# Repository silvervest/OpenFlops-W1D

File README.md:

# OpenFlops W1D
OpenFlops is an Open Hardware Floppy Disk Drive emulator/simulator.

OpenFlops W1D is a complete modification for the original OpenFlops specifically configured for use replacing the flaky Citizen W1D floppy drives, popularly used in Compaq LTE Elite laptops.

For a lot more detail, installation and usage guides, visit https://silvestron.com/openflops-w1d/

## Specifics to W1D

While this design is specifically made for the W1D when used in an LTE Elite laptop, it definitely can be used with any other floppy drive that uses the 26-pin FPC connector, it just may not fit in the same space. Heed caution.

Additionally, I made this with a few specific parts in mind - they are as follows:

* J1 - 26-pin FPC connector, part no. PCB-C5-26-SA-SMT
* J2 - USB-A port, part no. GCT USB1046
* J7 - microSD slot, part no. TF-114
* OLED - Any generic 128x64 0.96" OLED (WAVGAT on AliExpress)
* SPKR1 - Piezo buzzer, part no. CPT-9019S-SMT-TR
* SW3 - Slide switch, part no. MSK-12C02

## The rest of this README is from upstream OpenFlops!

See https://github.com/SukkoPera/OpenFlops/

### Summary
From [Wikipedia](https://en.wikipedia.org/wiki/Floppy_disk_hardware_emulator):
> Older models of computers, electronic keyboards and industrial automation often used floppy disk drives for data transfer. Older equipment may be difficult to replace or upgrade because of cost, requirement for continuous availability or unavailable upgrades. Proper operation may require operating system, software and data to be read and written from and to floppies, forcing users to maintain floppy drives on supporting systems.

> Floppy disks and floppy drives are gradually going out of production, and replacement of malfunctioning drives, and the systems hosting them, is becoming increasingly difficult. Floppy disks themselves are fragile, or may need to be replaced often. An alternative is to use a floppy disk hardware emulator, a device which appears to be a standard floppy drive to the old equipment by interfacing directly to the floppy disk controller, while storing data in another medium such as a USB thumb drive, Secure Digital card, or a shared drive on a computer network. Emulators can also be used as a higher-performance replacement for mechanical floppy disk drives. 

OpenFlops is an Open Hardware implementation of such an emulator, inspired from the ubiquitous Gotek hardware. It is designed to run the [FlashFloppy](https://github.com/keirf/FlashFloppy) firmware, which gives it several improvements over the original Gotek:
- Can be installed on [many different platforms](https://github.com/keirf/FlashFloppy/wiki/Host-Platforms)
- Directly supports a [wide range of image formats](https://github.com/keirf/FlashFloppy/wiki/Image-Formats)
- [Flexible track layout](https://github.com/keirf/FlashFloppy/wiki/Track-Layouts) for Raw Sector Images
- [Extremely configurable](https://github.com/keirf/FlashFloppy/wiki/FF.CFG-Configuration-File)
- Supports [AutoSwap](https://github.com/keirf/FF_AutoSwap) for games with a large number of disks
- Easily accessible pin headers for connection of a [i2c display](https://github.com/keirf/FlashFloppy/wiki/Hardware-Mods#lcd-display) (either OLED or LCD), [rotary encoder](https://github.com/keirf/FlashFloppy/wiki/Hardware-Mods#rotary-encoder) (including power)
- Built-in amplified speaker, or easily-accessible pin header for an external one
- USB connector can either be soldered on the board or connected to a pin header
- Connected Motor signal
- Emulates two drives at the same time (Not yet supported by the firmware, but [it will come](https://github.com/keirf/FlashFloppy/wiki/Donations))
- Has additional 3.3V, 5V and GND power pins
- And hey, it's Open Hardware!

All of this comes in the same form factor (and mounting holes) as the board installed in the original Gotek, hence it can be easily installed in any shell or enclosure designed for it.

### Assembly and Installation
Solder all components to the board. I suggest starting with the main microcontroller (U3), as it uses an LQFP package which is tricky to solder: the recommended technique is drag soldering, there are many videos about that on YouTube, so please look there for advice. I recommend soldering the bare minimum components needed for programming and then trying to flash it right away. This way you will be able to fix your soldering without too many components getting in the way, if needed. You will need a USB/TTL Serial converter for this: one with 3.3V I/O level is recommended, but a 5V one can be used, too (most pins on STM32 microcontrollers are 5V-tolerant, so don't worry, it's not a bad hack!). You shouldn't pay more than 1-2€ for it in any case, anyway. So, when you are ready:

- Solder U3, Y1, C3 and C5, then the programming header (the top one with power, BOOT0, TX, RX, etc.)
- Check for shorts on the 3.3V power lines, you can easily do this on the pads for C6-C10
- If your USB/Serial adapter has a 3.3V output, connect it to 3.3V on the power header, then connect ground, RX and TX
- If no 3.3V output is available, solder U4 and power the board through the 5V pin on the power header

Now you should be able to [program the STM32 microcontroller](https://github.com/keirf/FlashFloppy/wiki/Firmware-Programming). If you have difficultes you can try adding R10 (and C4) and maybe a few of C6-C10, but most likely the problem will be with the solder joints on U3, as soldering this kind of package manually is never easy, so please get a lens (or even better, a microscope) and double-check your job.

The serial adapter is only necessary for the first flashing. Subsequent updates [can be done easily via USB](https://github.com/keirf/FlashFloppy/wiki/Firmware-Update).

Note that most components are necessary, but there are a few you can skip if you are feeling lazy:
- If you are not interested in the head movement sound, you can skip the following components: SPK1, D2, R5, R6, Q7.
- If your LCD/OLED display already has pull-up resistors for the SDA/SCK lines (most do), you can skip R3 and R4.

### Configuration
Please refer to the FlashFloppy wiki for the [initial setup](https://github.com/keirf/FlashFloppy/wiki/Initial-Setup) and an overview of the [available configuration options](https://github.com/keirf/FlashFloppy/wiki/FF.CFG-Configuration-File).

Some options that you will want to override the default values of, in order to take advantage of all the features OpenFlops provides, are the following:
- `motor-delay`
- `rotary`
- `display-type`

### Releases
If you want to get this board produced, you are recommended to get [the latest release](https://github.com/SukkoPera/OpenFlops/releases) rather than the current git version, as the latter might be under development and is not guaranteed to be working.

Every release is accompanied by its Bill Of Materials (BOM) file and any relevant notes about it, which you are recommended to read carefully.

### License
The OpenFlops documentation, including the design itself, is copyright &copy; SukkoPera 2019-2020.

OpenFlops is Open Hardware licensed under the [CERN OHL v. 1.2](http://ohwr.org/cernohl).

You may redistribute and modify this documentation under the terms of the CERN OHL v.1.2. This documentation is distributed *as is* and WITHOUT ANY EXPRESS OR IMPLIED WARRANTIES whatsoever with respect to its functionality, operability or use, including, without limitation, any implied warranties OF MERCHANTABILITY, SATISFACTORY QUALITY, FITNESS FOR A PARTICULAR PURPOSE or infringement. We expressly disclaim any liability whatsoever for any direct, indirect, consequential, incidental or special damages, including, without limitation, lost revenues, lost profits, losses resulting from business interruption or loss of data, regardless of the form of action or legal theory under which the liability may be asserted, even if advised of the possibility or likelihood of such damages.

A copy of the full license is included in file [LICENSE.pdf](LICENSE.pdf), please refer to it for applicable conditions. In order to properly deal with its terms, please see file [LICENSE_HOWTO.pdf](LICENSE_HOWTO.pdf).

The contact points for information about manufactured Products (see section 4.2) are listed in file [PRODUCT.md](PRODUCT.md).

Any modifications made by Licensees (see section 3.4.b) shall be recorded in file [CHANGES.md](CHANGES.md).

The Documentation Location of the original project is https://github.com/SukkoPera/OpenFlops/.

### Support the Project
Since the project is open you are free to get the PCBs made by your preferred manufacturer, however in case you want to support the development, you can order them from PCBWay through this link:

You get my gratitude and cheap, professionally-made and good quality PCBs, I get some credit that will help with this and [other projects](https://www.pcbway.com/project/member/shareproject/?bmbid=41100). You won't even have to worry about the various PCB options, it's all pre-configured for you!

Also, if you still have to register to that site, [you can use this link](https://www.pcbway.com/setinvite.aspx?inviteid=41100) to get some bonus initial credit (and yield me some more).

Again, if you want to use another manufacturer, feel free to, don't feel obligated :). But then you can buy me a coffee if you want:

### Get Help
If you need help or have questions, you can join [the official Telegram group](https://t.me/joinchat/HUHdWBC9J9JnYIrvTYfZmg).

### Thanks
- H.M for publishing the [original Gotek schematics](doc/gotek_usb-fde_block-diagram.jpg)
- [keirf](https://github.com/keirf) for FlashFloppy
- Brian Allan for suggesting some improvements for the Speaker circuit
- Ray Bellis for suggesting adding pin headers for the USB port and speaker
- Mario Babeu for suggesting to line up the orientation of LD1 and LD2
- Patrick Kerkhof for sending me a lot of original Gotek housing for dimensional testing

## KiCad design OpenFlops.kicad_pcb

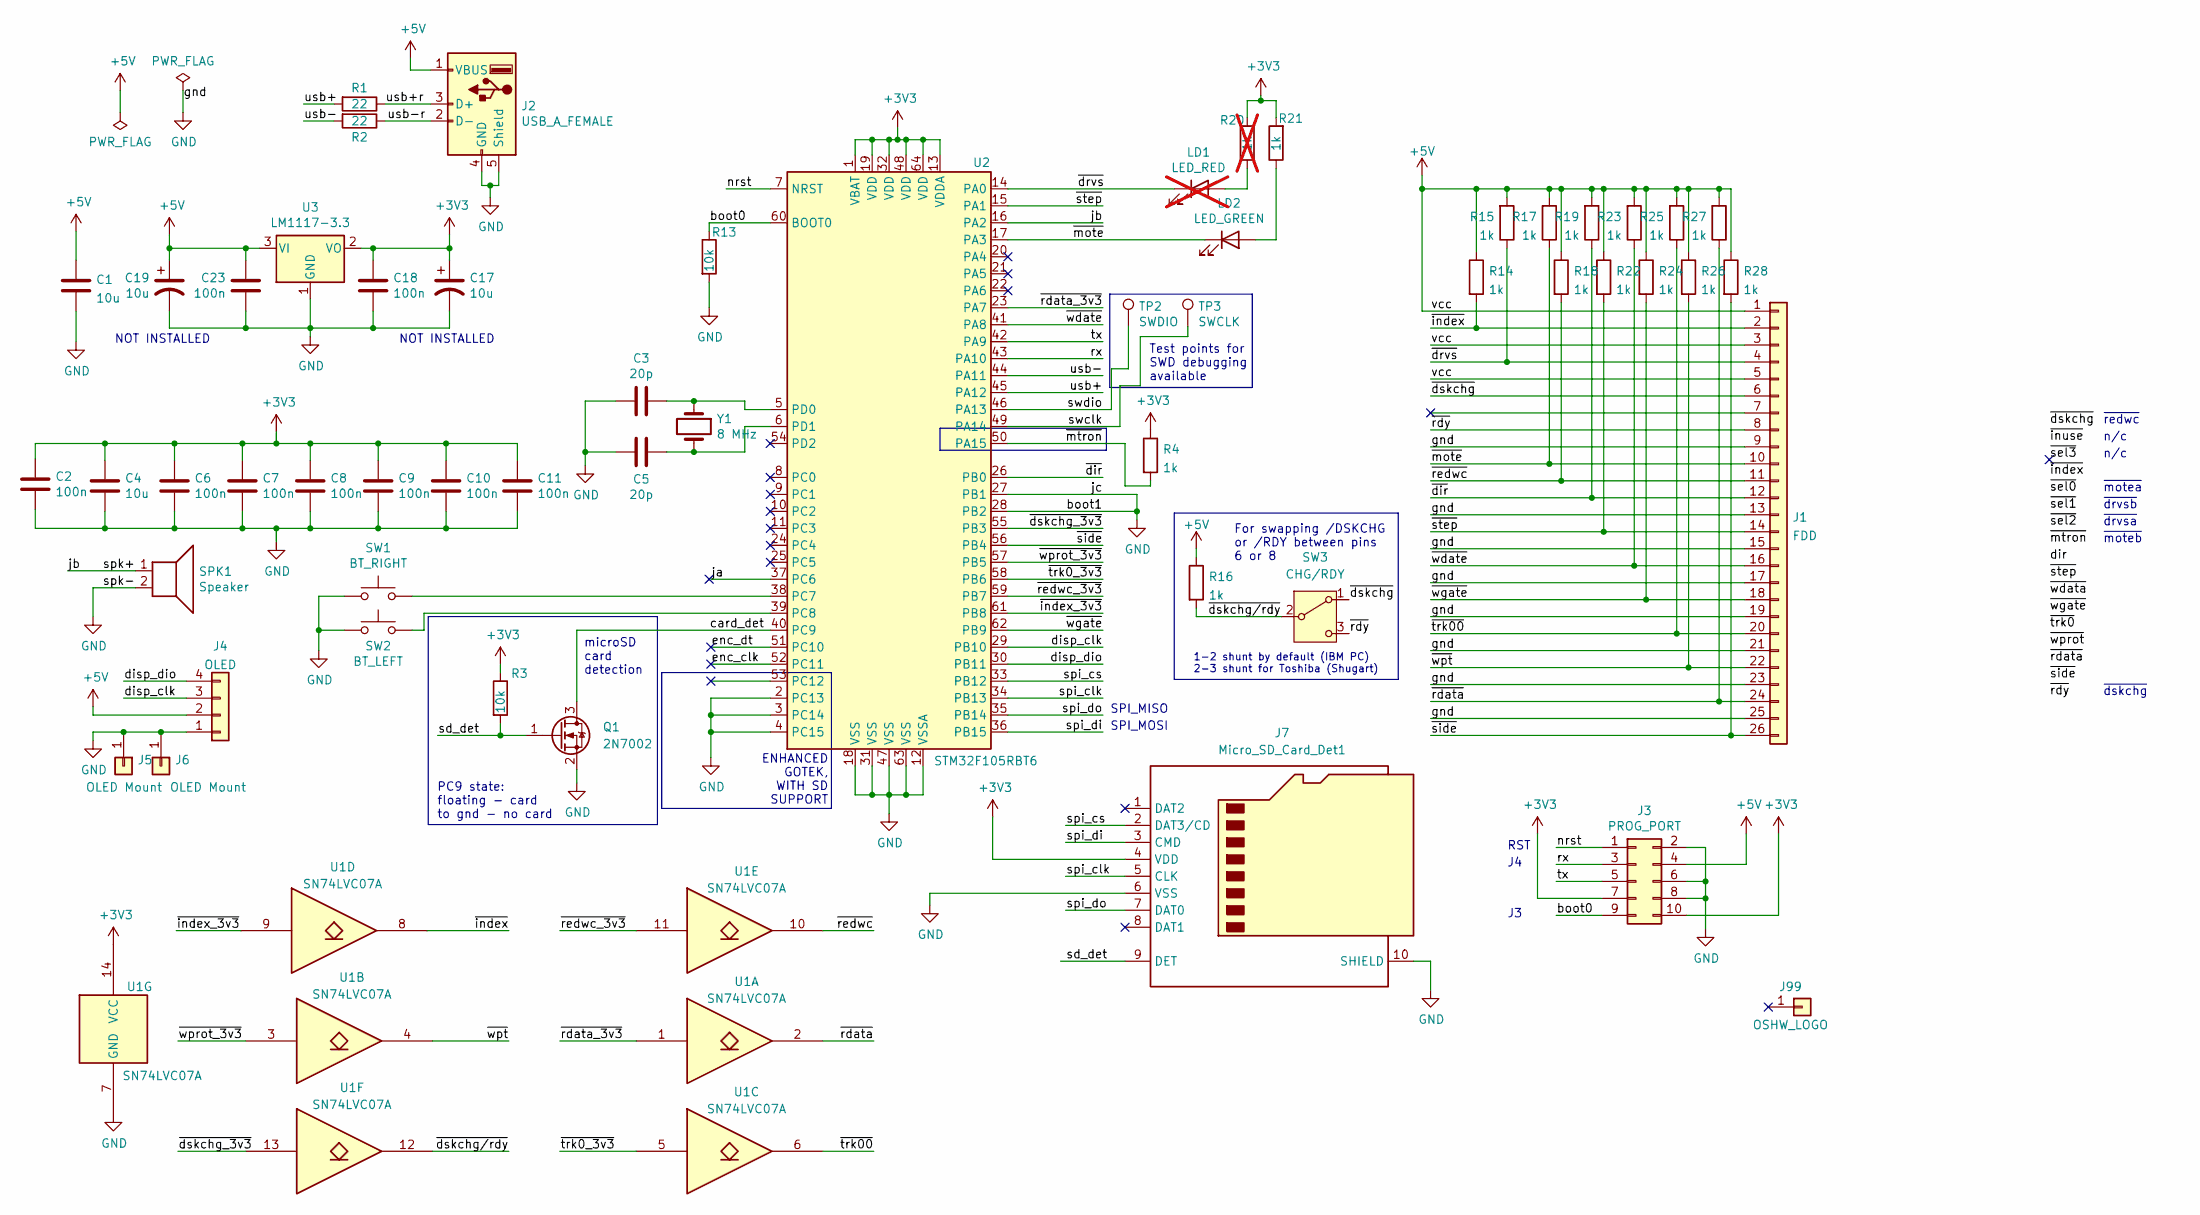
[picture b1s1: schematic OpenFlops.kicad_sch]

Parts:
C1, C4: 10u; C_0805_2012Metric_Pad1.18x1.45mm_HandSolder; LCSC C15850
C2, C6, C7, C8, C9, C10, C11, C18, C23: 100n; C_0805_2012Metric_Pad1.18x1.45mm_HandSolder; MFG Part Num MULTILAYER CERAMIC CAPACITORS MLCC - SM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; JLCPCB PN CC0805KRX7R9BB104
C3, C5: 20p; C_0805_2012Metric_Pad1.18x1.45mm_HandSolder; MFG Part Num MULTILAYER CERAMIC CAPACITORS MLCC - SM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; JLCPCB PN CC0805KRX7R9BB221
C17, C19: 10u; CP_Elec_4x5.4
J1: FDD; Adam_Tech_PCB-C5-26-SA-SMT_1x26_P1.00mm_Horizontal; LCSC C19188849
J2: USB_A_FEMALE; USB_A_TE_292303-7_Horizontal; LCSC C2763369
J3: PROG_PORT; PinHeader_2x05_P2.54mm_Vertical
J4: OLED; PinHeader_1x04_P2.54mm_Vertical
J5, J6: OLED Mount; TestPoint_Pad_4.0x4.0mm
J7: Micro_SD_Card_Det1; microSD_XUNPU_TF-114; LCSC C266619
J99: OSHW_LOGO; OSHW-Logo2_9.8x8mm_Copper
LD1: LED_RED; LED_0805_2012Metric; not fitted
LD2: LED_GREEN; LED_0805_2012Metric; LCSC C2297
Q1: 2N7002; SOT-23; LCSC C8545
R1, R2: 22; R_0805_2012Metric_Pad1.20x1.40mm_HandSolder; MFG Part Num CHIP RESISTOR - SURFACE MOUNT 22OHMS ±1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; JLCPCB PN 0805W8F220JT5E
R3: 10k; R_0805_2012Metric_Pad1.20x1.40mm_HandSolder; LCSC C17414
R4, R14: 1k; R_0805_2012Metric_Pad1.20x1.40mm_HandSolder; LCSC C17513
R13: 10k; R_0805_2012Metric_Pad1.20x1.40mm_HandSolder
R15, R16, R17, R18, R19, R21, R22, R23, R24, R25, R26, R27, R28: 1k; R_0805_2012Metric_Pad1.20x1.40mm_HandSolder
R20: 1k; R_0805_2012Metric_Pad1.20x1.40mm_HandSolder; not fitted
SPK1: Speaker; Buzzer_CUI_CPT-9019S-SMT; LCSC C968734
SW1: BT_RIGHT; SW_Tactile_SPST_Angled_PTS645Vx83-2LFS
SW2: BT_LEFT; SW_Tactile_SPST_Angled_PTS645Vx83-2LFS; LCSC C125034
SW3: CHG/RDY; SW_SPDT_PCM12; LCSC C22435662
TP2: SWDIO; TestPoint_Pad_D1.0mm
TP3: SWCLK; TestPoint_Pad_D1.0mm
U1: SN74LVC07A; TSSOP-14_4.4x5mm_P0.65mm; LCSC C1548107
U2: STM32F105RBT6; LQFP-64_10x10mm_P0.5mm; MFG Part Num ST MICROELECTRONICS LQFP-64_10X10X05P R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; JLCPCB PN STM32F105RBT6
U3: LM1117-3.3; SOT-223-3_TabPin2; MFG Part Num LOW DROPOUT REGULATORS(LDO) POSITIVE FI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; JLCPCB PN AMS1117-3.3
Y1: 8 MHz; Crystal_SMD_5032-2Pin_5.0x3.2mm_HandSoldering; LCSC C115962

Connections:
+3V3: C2.1, C4.1, C6.1, C7.1, C8.1, C9.1, C10.1, C11.1, C17.1, C18.1, J3.7, J3.10, J7.4 (VDD), R3.1, R4.1, R20.2, R21.2, U1.14 (VCC), U2.1 (VBAT), U2.13 (VDDA), U2.19 (VDD), U2.32 (VDD), U2.48 (VDD), U2.64 (VDD), U3.2 (VO)
+5V: C1.1, C19.1, C23.1, J1.1, J1.3, J1.5, J2.1 (VBUS), J3.4, J4.2, R14.1, R15.2, R16.1, R17.2, R18.1, R19.2, R22.1, R23.2, R24.1, R25.2, R26.1, R27.2, R28.1, U3.3 (VI)
/boot0: J3.9, R13.1, U2.60 (BOOT0)
/card_det: Q1.3 (D), U2.40 (PC9)
/disp_clk: J4.3, U2.29 (PB10)
/disp_dio: J4.4, U2.30 (PB11)
/enc_clk: U2.52 (PC11)
/enc_dt: U2.51 (PC10)
/ja: U2.37 (PC6)
/jb: SPK1.1, U2.16 (PA2)
/nrst: J3.1, U2.7 (NRST)
/rx: J3.3, U2.43 (PA10)
/sd_det: J7.9 (DET), Q1.1 (G), R3.2
/spi_clk: J7.5 (CLK), U2.34 (PB13)
/spi_cs: J7.2 (DAT3/CD), U2.33 (PB12)
/spi_di: J7.3 (CMD), U2.36 (PB15)
/spi_do: J7.7 (DAT0), U2.35 (PB14)
/swclk: TP3.1, U2.49 (PA14)
/swdio: TP2.1, U2.46 (PA13)
/tx: J3.5, U2.42 (PA9)
/usb+: R1.2, U2.45 (PA12)
/usb+r: J2.3 (D+), R1.1
/usb-: R2.2, U2.44 (PA11)
/usb-r: J2.2 (D-), R2.1
/~dir: J1.12, R19.1, U2.26 (PB0)
/~drvs: J1.4, LD1.1 (K), R15.1, U2.14 (PA0)
/~dskchg_3v3: U1.13, U2.55 (PB3)
/~dskchg/rdy: R16.2, SW3.2 (B), U1.12
/~dskchg: J1.6, SW3.1 (A)
/~index_3v3: U1.9, U2.61 (PB8)
/~index: J1.2, R14.2, U1.8
/~mote: J1.10, LD2.1 (K), R17.1, U2.17 (PA3)
/~mtron: R4.2, U2.50 (PA15)
/~rdata_3v3: U1.1, U2.23 (PA7)
/~rdata: J1.24, R27.1, U1.2
/~rdy: J1.8, SW3.3 (C)
/~redwc_3v3: U1.11, U2.59 (PB7)
/~redwc: J1.11, R18.2, U1.10
/~side: J1.26, R28.2, U2.56 (PB4)
/~step: J1.14, R22.2, U2.15 (PA1)
/~trk0_3v3: U1.5, U2.58 (PB6)
/~trk00: J1.20, R25.1, U1.6
/~wdate: J1.16, R23.1, U2.41 (PA8)
/~wgate: J1.18, R24.2, U2.62 (PB9)
/~wprot_3v3: U1.3, U2.57 (PB5)
/~wpt: J1.22, R26.2, U1.4
GND: C1.2, C2.2, C3.2, C4.2, C5.2, C6.2, C7.2, C8.2, C9.2, C10.2, C11.2, C17.2, C18.2, C19.2, C23.2, J1.9, J1.13, J1.15, J1.17, J1.19, J1.21, J1.23, J1.25, J2.4 (GND), J2.5 (Shield), J3.2, J3.6, J3.8, J4.1, J5.1, J6.1, J7.6 (VSS), J7.10 (SHIELD), Q1.2 (S), R13.2, SPK1.2, SW1.1, SW2.1, U1.7 (GND), U2.2 (PC13), U2.3 (PC14), U2.4 (PC15), U2.12 (VSSA), U2.18 (VSS), U2.27 (PB1), U2.28 (PB2), U2.31 (VSS), U2.47 (VSS), U2.63 (VSS), U3.1 (GND)
unnamed: LD1.2 (A), R20.1
unnamed: LD2.2 (A), R21.1
unnamed: SW1.2, U2.38 (PC7)
unnamed: SW2.2, U2.39 (PC8)
unnamed: C3.1, U2.5 (PD0), Y1.1
unnamed: C5.1, U2.6 (PD1), Y1.2

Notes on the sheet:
~{dskchg}
n/c
~{drvsa}
RST
ENHANCED GOTEK, WITH SD SUPPORT
microSD card detection
PC9 state: floating - card to gnd - no card
SPI_MISO
SPI_MOSI
~{redwc}
For swapping /DSKCHG or /RDY between pins 6 or 8
Test points for SWD debugging available
NOT INSTALLED
~{moteb}
1-2 shunt by default (IBM PC) 2-3 shunt for Toshiba (Shugart)
~{motea}
~{drvsb}

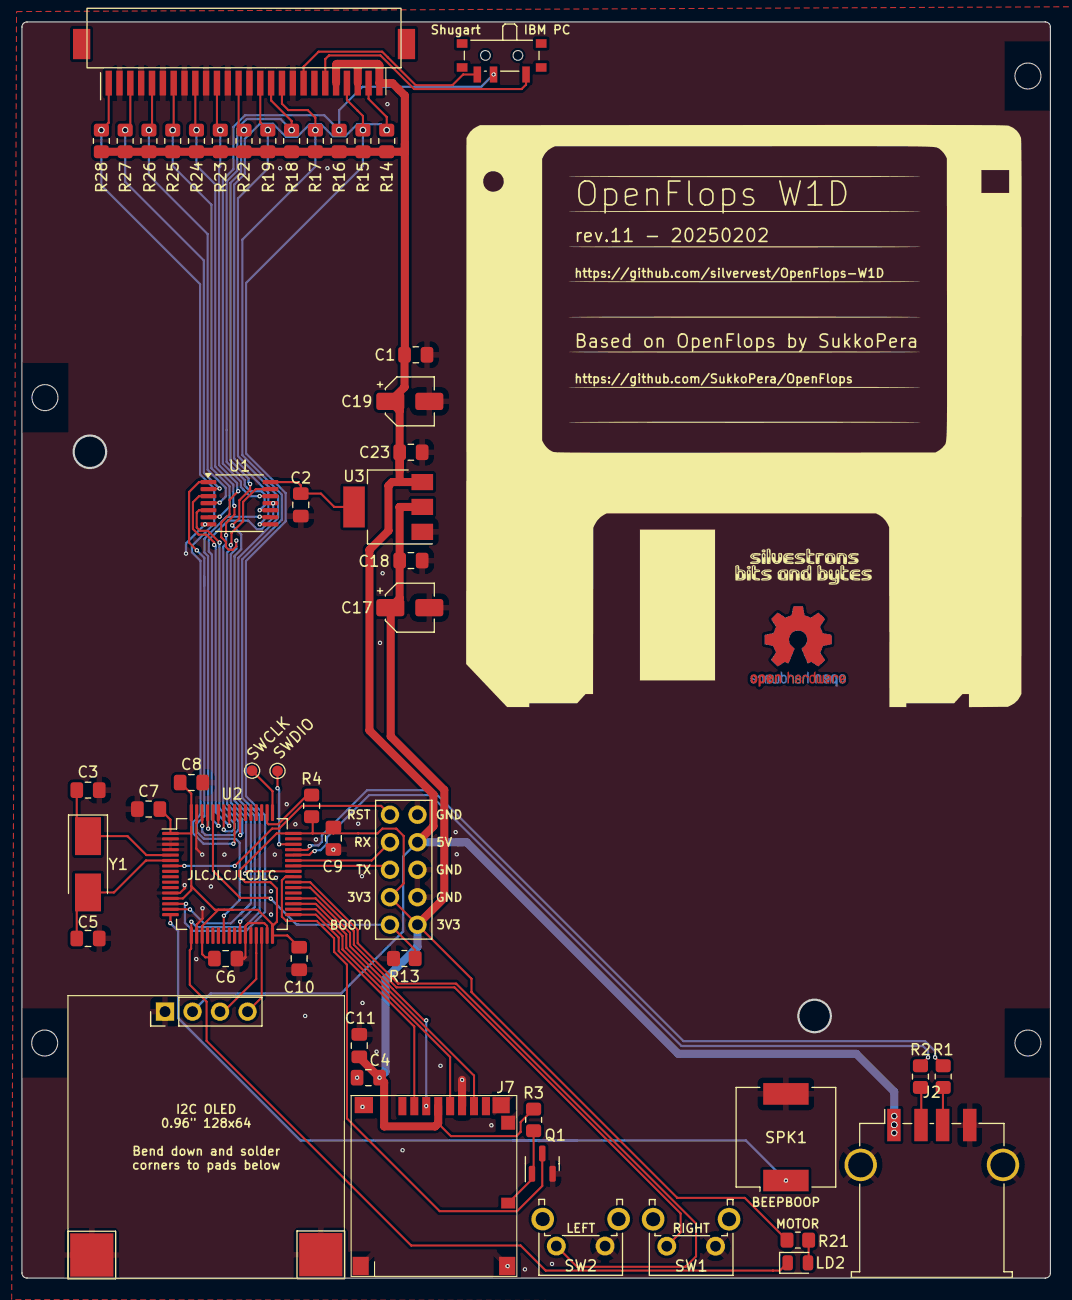
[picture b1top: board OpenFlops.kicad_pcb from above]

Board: 2 copper layers, 94.8 x 115.8 mm, 55 parts (1 on the bottom side), 49 nets.

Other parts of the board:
J99#2: OSHW_LOGO; OSHW-Logo2_9.8x8mm_Copper

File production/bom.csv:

Designator,Footprint,Quantity,Value,LCSC Part #
"C1, C4",0805,2,10u,C15850
"C10, C11, C18, C23, C6, C7, C8, C9",0805,8,100n,
"C17, C19",CP_Elec_4x5.4,2,10u,
C2,0805,1,100n,C49678
"C3, C5",0805,2,20p,C107145
J1,Adam_Tech_PCB-C5-26-SA-SMT_1x26_P1.00mm_Horizontal,1,FDD,
J2,USB_A_TE_292303-7_Horizontal,1,USB_A_FEMALE,C42637
J3,PinHeader_2x05_P2.54mm_Vertical,1,PROG_PORT,
J4,PinHeader_1x04_P2.54mm_Vertical,1,OLED,
"J5, J6",TestPoint_Pad_4.0x4.0mm,2,OLED Mount,
J7,microSD_XUNPU_TF-114,1,Micro_SD_Card_Det1,C266619
"J99_2, J99",OSHW-Logo2_9.8x8mm_Copper,2,OSHW_LOGO,
LD2,0805,1,LED_GREEN,C2297
Q1,SOT-23,1,2N7002,C8545
R1,0805,1,22,C17561
R13,0805,1,10k,
"R14, R4",0805,2,1k,C17513
"R15, R16, R17, R18, R19, R21, R22, R23, R24, R25, R26, R27, R28",0805,13,1k,
R2,0805,1,22,
R3,0805,1,10k,C17414
SPK1,Buzzer_CUI_CPT-9019S-SMT,1,Speaker,
SW1,SW_Tactile_SPST_Angled_PTS645Vx83-2LFS,1,BT_RIGHT,
SW2,SW_Tactile_SPST_Angled_PTS645Vx83-2LFS,1,BT_LEFT,
SW3,SW_SPDT_PCM12,1,CHG/RDY,C22435662
TP2,TestPoint_Pad_D1.0mm,1,SWDIO,
TP3,TestPoint_Pad_D1.0mm,1,SWCLK,
U1,TSSOP-14_4.4x5mm_P0.65mm,1,SN74LVC07A,C7659
U2,LQFP-64_10x10mm_P0.5mm,1,STM32F105RBT6,C8349
U3,SOT-223-3_TabPin2,1,LM1117-3.3,C6186
Y1,Crystal_SMD_5032-2Pin_5.0x3.2mm_HandSoldering,1,8 MHz,C115962

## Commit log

2022-03-11 updated to kicad 6; dual mount smt/tht crystal; added test points for swd
2023-04-02 update for citizen w1d
2023-04-18 updating to fix a few cut ground traces
2024-12-02 rev 10; more smd for more assembly
2024-12-02 update images
2024-12-02 link to blog post
2024-12-02 update specific parts
2025-02-20 rev 11; fixed issue with usb port being too far forward

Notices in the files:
OpenFlops.kicad_pcb:
Licensed under CERN OHL v.1.2
